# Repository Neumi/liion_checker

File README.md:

# 18650 Battery Checker 
A 18650 Li-Ion battery checker and charger that can be loaded and unloaded by a robotic gripper. Up to 127 devices can be connected on one i2c bus to exchange test results with a master that is connected to a SPS/Arduino/Raspberry Pi.

## Main features:
 - TP4056 charger up to 1A charge current
 - discharging with a programmable constant current sink
 - i2c interconnectivity to other chargers and a master
 - 18650 cells can be placed/removed by a robotic gripper

## Images

### Sorting Machine

### Layout and Board

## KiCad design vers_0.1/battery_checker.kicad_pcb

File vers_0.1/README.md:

# Version 0.1
Basic functionality works. Code is not fully implemented yet.

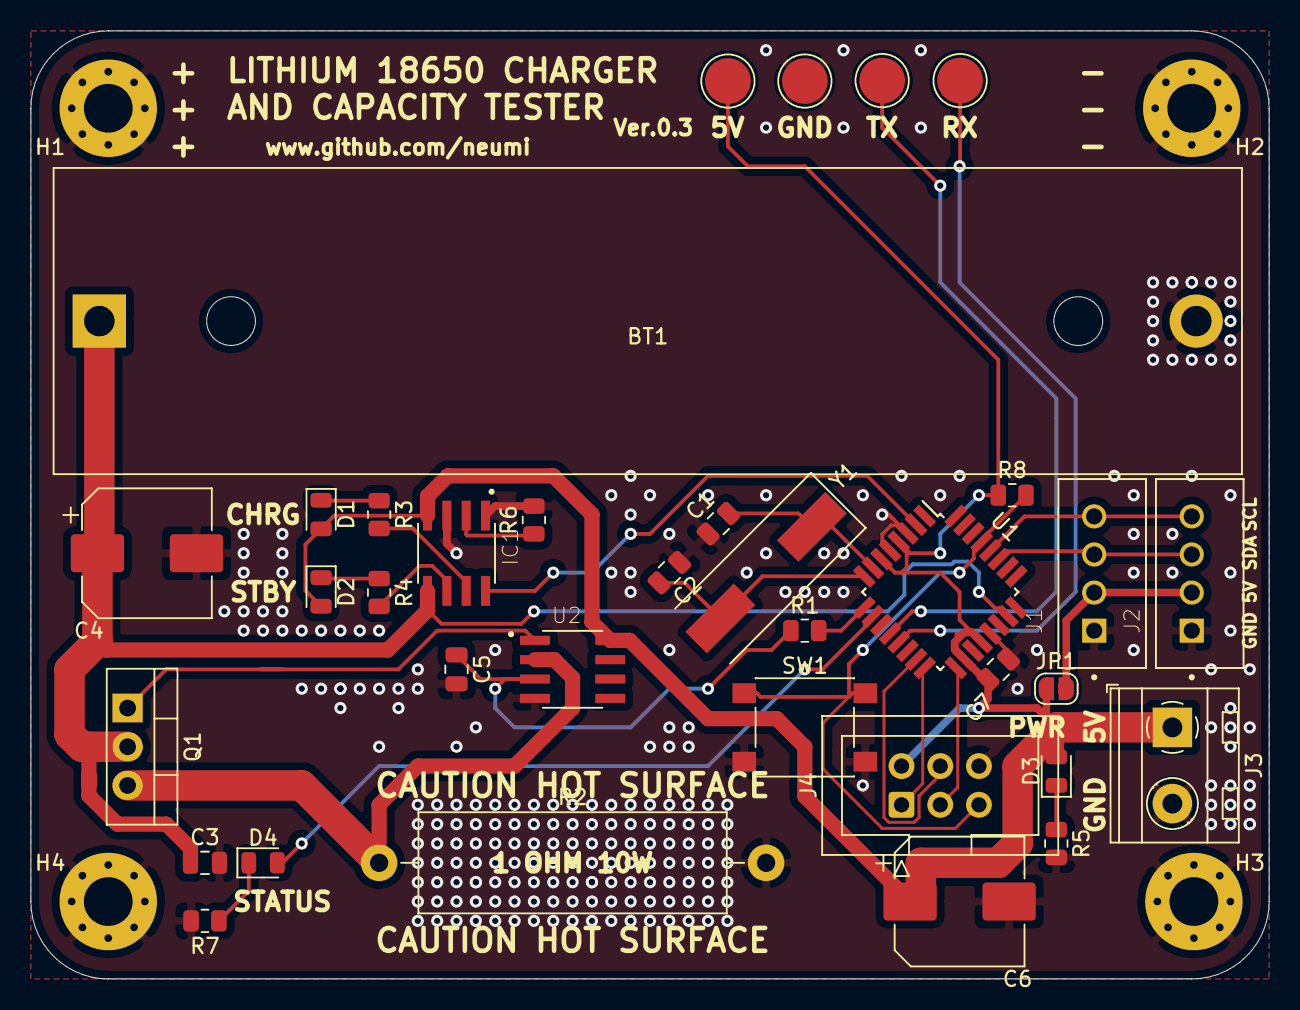
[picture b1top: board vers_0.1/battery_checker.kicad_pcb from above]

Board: 2 copper layers, 81.3 x 62.2 mm, 39 parts (0 on the bottom side), 27 nets.

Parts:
BT1: Battery_Cell; BatteryHolder_MPD_BH-18650-PC2
C1, C2: 22p; C_0805_2012Metric
C3, C5, C7: 100nF; C_0805_2012Metric
C4, C6: 220uF; CP_Elec_8x10
D1: LED_CHRG; LED_0805_2012Metric
D2: LED_STDBY; LED_0805_2012Metric
D3: LED_PWR; LED_0805_2012Metric
D4: LED_STATUS; LED_0805_2012Metric
H1, H2, H3, H4: MountingHole_Pad; MountingHole_3.2mm_M3_Pad_Via
IC1: TP4056; SOIC127P599X175-8N
J1, J2: B4B-XH-A(LF)(SN); JST_B4B-XH-A(LF)(SN)
J3: Conn_01x02_Male; TerminalBlock_MetzConnect_Type094_RT03502HBLU_1x02_P5.00mm_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
J4: AVR-ISP-6; IDC-Header_2x03_P2.54mm_Vertical
JP1: SolderJumper_2_Open; SolderJumper-2_P1.3mm_Open_RoundedPad1.0x1.5mm
Q1: IRLZ44N; TO-220-3_Vertical
R1: 1M; R_0805_2012Metric
R2: 1R5W; R_Axial_Power_L20.0mm_W6.4mm_P25.40mm
R3, R4, R5, R7: 330; R_0805_2012Metric
R6: 1.5k; R_0805_2012Metric
R8: 10k; R_0805_2012Metric
SW1: reset; SW_Push_1P1T_NO_6x6mm_H9.5mm
TP1: 5V; TestPoint_Pad_D3.0mm
TP2: GND; TestPoint_Pad_D3.0mm
TP3: RX; TestPoint_Pad_D3.0mm
TP4: TX; TestPoint_Pad_D3.0mm
U1: ATmega328-AU; TQFP-32_7x7mm_P0.8mm
U2: LM358M_NOPB; SOIC127P599X175-8N
Y1: Crystal; Crystal_SMD_HC49-SD

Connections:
+5V: C6.1, C7.1, D1.2, D2.2, D3.2, IC1.4, J3.1, J4.2, JP1.1, R8.1, TP1.1, U1.4, U1.6, U1.18, U1.20, U2.8
CHRG_enable: IC1.8, U1.2
GND: BT1.2, C1.1, C2.1, C3.2, C4.2, C5.2, C6.2, C7.2, H1.1, H2.1, H3.1, H4.1, IC1.1, IC1.3, J1.1, J2.1, J3.2, J4.6, R2.2, R5.2, R6.2, R7.2, SW1.2, TP2.1, U1.3, U1.5, U1.21, U2.4
LED_STATUS: D4.2, U1.10
MISO: J4.1, U1.16
MOSI: J4.4, U1.15
unnamed: C1.2, U1.7, Y1.1
unnamed: C2.2, U1.8, Y1.2
unnamed: C5.1, R1.1, U2.3
unnamed: D1.1, R3.1
unnamed: D2.1, R4.1
unnamed: D3.1, R5.1
unnamed: D4.1, R7.1
unnamed: IC1.2, R6.1
unnamed: IC1.6, R4.2
unnamed: IC1.7, R3.2
unnamed: J1.2, J2.2, JP1.2
unnamed: Q1.1, U2.1
unnamed: Q1.3, R2.1, U2.2
PWM: R1.2, U1.9
RST: J4.5, R8.2, SW1.1, U1.29
RX: TP3.1, U1.13
SCK: J4.3, U1.17
SCL: J1.4, J2.4, U1.28
SDA: J1.3, J2.3, U1.27
TX: TP4.1, U1.12
v_sens: BT1.1, C3.1, C4.1, IC1.5, Q1.2, U1.23

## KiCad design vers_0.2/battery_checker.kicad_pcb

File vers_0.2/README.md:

# Version 0.2
Version 0.2 is a four battery approach with only one microcontroller that manages charging/discharging/measurements for all four cells at once.

Board needs layout. Schematic is done.

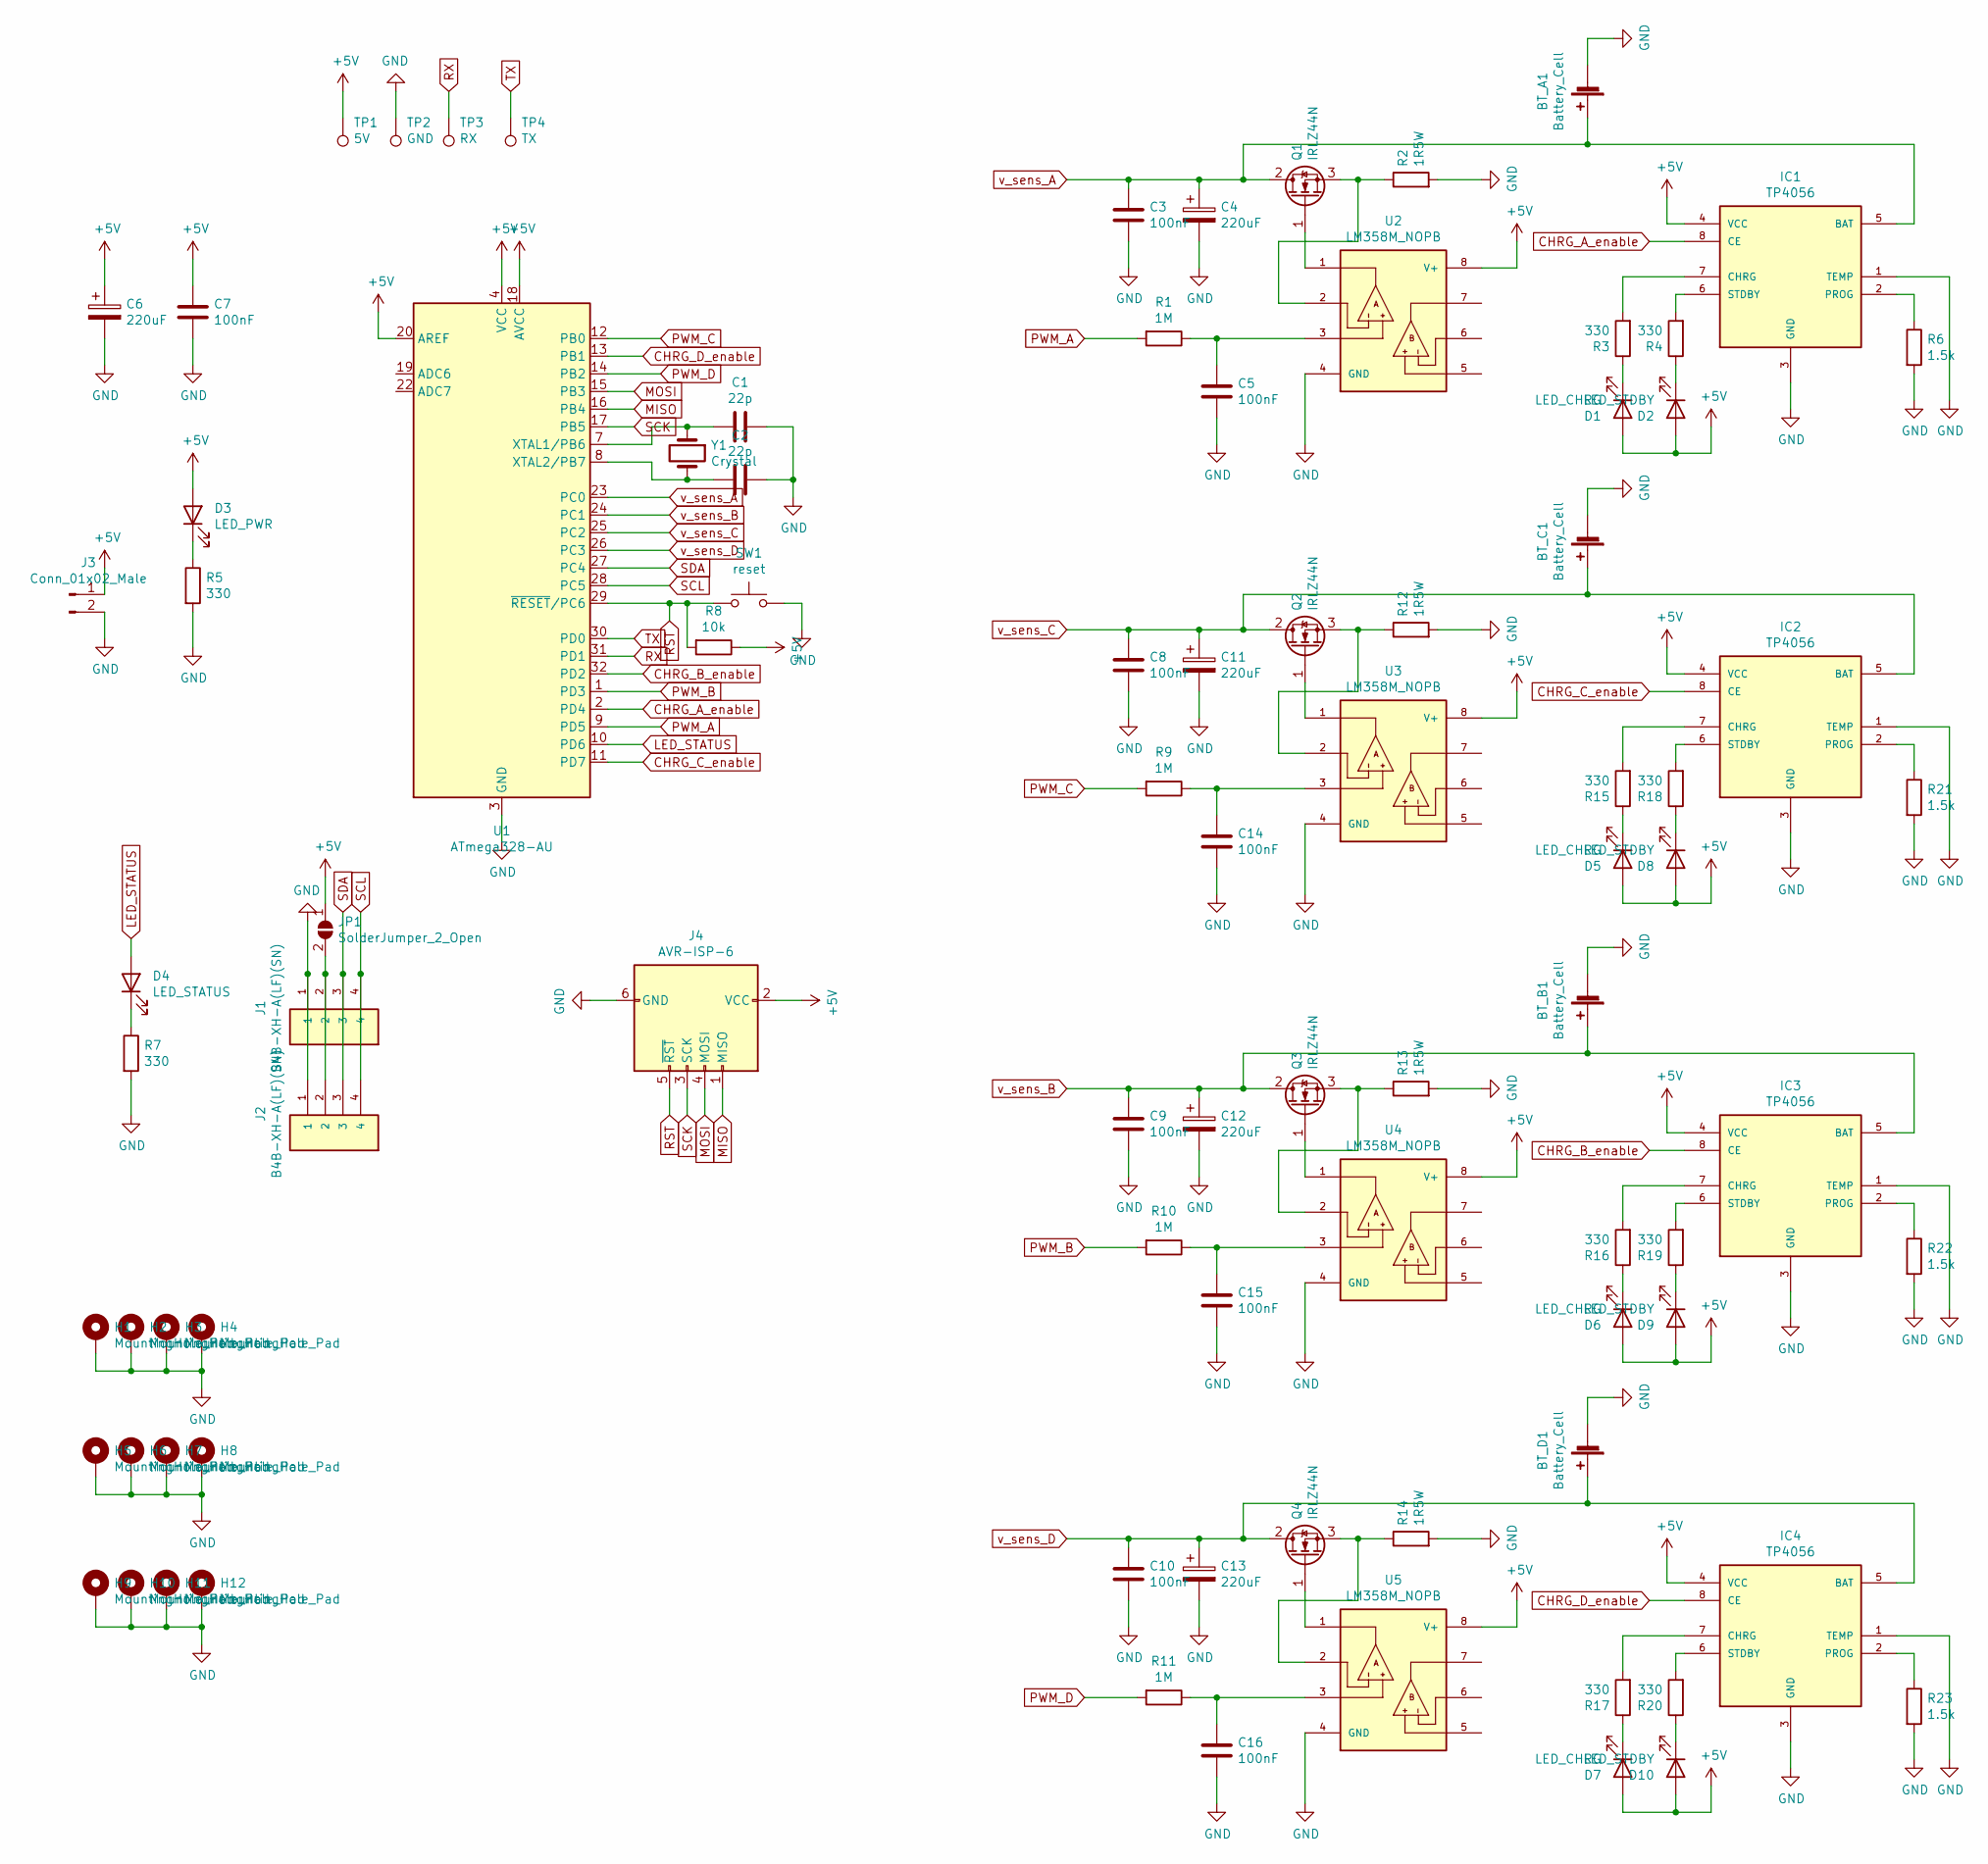
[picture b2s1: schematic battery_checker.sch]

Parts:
BT_A1: Battery_Cell; BatteryHolder_MPD_BH-18650-PC2
BT_B1: Battery_Cell; BatteryHolder_MPD_BH-18650-PC2
BT_C1: Battery_Cell; BatteryHolder_MPD_BH-18650-PC2
BT_D1: Battery_Cell; BatteryHolder_MPD_BH-18650-PC2
C1, C2: 22p; C_0805_2012Metric
C3, C5, C7, C8, C9, C10, C14, C15, C16: 100nF; C_0805_2012Metric
C4, C6, C11, C12, C13: 220uF; CP_Elec_8x10
D1, D5, D6, D7: LED_CHRG; LED_0805_2012Metric
D2, D8, D9, D10: LED_STDBY; LED_0805_2012Metric
D3: LED_PWR; LED_0805_2012Metric
D4: LED_STATUS; LED_0805_2012Metric
H1, H2, H3, H4, H5, H6, H7, H8, H9, H10, H11, H12: MountingHole_Pad; MountingHole_3.2mm_M3_Pad_Via
IC1, IC2, IC3, IC4: TP4056; SOIC127P599X175-8N
J1, J2: B4B-XH-A(LF)(SN); JST_B4B-XH-A(LF)(SN); PARTREV NA
J3: Conn_01x02_Male; TerminalBlock_MetzConnect_Type094_RT03502HBLU_1x02_P5.00mm_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
J4: AVR-ISP-6; IDC-Header_2x03_P2.54mm_Vertical
JP1: SolderJumper_2_Open; SolderJumper-2_P1.3mm_Open_RoundedPad1.0x1.5mm
Q1, Q2, Q3, Q4: IRLZ44N; TO-220-3_Vertical
R1, R9, R10, R11: 1M; R_0805_2012Metric
R2, R12, R13, R14: 1R5W; R_Axial_Power_L20.0mm_W6.4mm_P25.40mm
R3, R4, R5, R7, R15, R16, R17, R18, R19, R20: 330; R_0805_2012Metric
R6, R21, R22, R23: 1.5k; R_0805_2012Metric
R8: 10k; R_0805_2012Metric
SW1: reset; SW_Push_1P1T_NO_6x6mm_H9.5mm
TP1: 5V; TestPoint_Pad_D3.0mm
TP2: GND; TestPoint_Pad_D3.0mm
TP3: RX; TestPoint_Pad_D3.0mm
TP4: TX; TestPoint_Pad_D3.0mm
U1: ATmega328-AU; TQFP-32_7x7mm_P0.8mm
U2, U3, U4, U5: LM358M_NOPB; SOIC127P599X175-8N
Y1: Crystal; Crystal_SMD_HC49-SD

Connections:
+5V: C6.1, C7.1, D1.2 (A), D2.2 (A), D3.2 (A), D5.2 (A), D6.2 (A), D7.2 (A), D8.2 (A), D9.2 (A), D10.2 (A), IC1.4 (VCC), IC2.4 (VCC), IC3.4 (VCC), IC4.4 (VCC), J3.1, J4.2 (VCC), JP1.1 (A), R8.1, TP1.1, U1.4 (VCC), U1.6 (VCC), U1.18 (AVCC), U1.20 (AREF), U2.8 (V+), U3.8 (V+), U4.8 (V+), U5.8 (V+)
CHRG_A_enable: IC1.8 (CE), U1.2 (PD4)
CHRG_B_enable: IC3.8 (CE), U1.32 (PD2)
CHRG_C_enable: IC2.8 (CE), U1.11 (PD7)
CHRG_D_enable: IC4.8 (CE), U1.13 (PB1)
GND: BT_A1.2 (-), BT_B1.2 (-), BT_C1.2 (-), BT_D1.2 (-), C1.1, C2.1, C3.2, C4.2, C5.2, C6.2, C7.2, C8.2, C9.2, C10.2, C11.2, C12.2, C13.2, C14.2, C15.2, C16.2, H1.1, H2.1, H3.1, H4.1, H5.1, H6.1, H7.1, H8.1, H9.1, H10.1, H11.1, H12.1, IC1.1 (TEMP), IC1.3 (GND), IC2.1 (TEMP), IC2.3 (GND), IC3.1 (TEMP), IC3.3 (GND), IC4.1 (TEMP), IC4.3 (GND), J1.1, J2.1, J3.2, J4.6 (GND), R2.2, R5.2, R6.2, R7.2, R12.2, R13.2, R14.2, R21.2, R22.2, R23.2, SW1.2, TP2.1, U1.3 (GND), U1.5 (GND), U1.21 (GND), U2.4 (GND), U3.4 (GND), U4.4 (GND), U5.4 (GND)
LED_STATUS: D4.2 (A), U1.10 (PD6)
MISO: J4.1 (MISO), U1.16 (PB4)
MOSI: J4.4 (MOSI), U1.15 (PB3)
unnamed: C1.2, U1.7 (XTAL1/PB6), Y1.1
unnamed: C2.2, U1.8 (XTAL2/PB7), Y1.2
unnamed: C5.1, R1.1, U2.3
unnamed: C14.1, R9.1, U3.3
unnamed: C15.1, R10.1, U4.3
unnamed: C16.1, R11.1, U5.3
unnamed: D1.1 (K), R3.1
unnamed: D2.1 (K), R4.1
unnamed: D3.1 (K), R5.1
unnamed: D4.1 (K), R7.1
unnamed: D5.1 (K), R15.1
unnamed: D6.1 (K), R16.1
unnamed: D7.1 (K), R17.1
unnamed: D8.1 (K), R18.1
unnamed: D9.1 (K), R19.1
unnamed: D10.1 (K), R20.1
unnamed: IC1.2 (PROG), R6.1
unnamed: IC1.6 (STDBY), R4.2
unnamed: IC1.7 (CHRG), R3.2
unnamed: IC2.2 (PROG), R21.1
unnamed: IC2.6 (STDBY), R18.2
unnamed: IC2.7 (CHRG), R15.2
unnamed: IC3.2 (PROG), R22.1
unnamed: IC3.6 (STDBY), R19.2
unnamed: IC3.7 (CHRG), R16.2
unnamed: IC4.2 (PROG), R23.1
unnamed: IC4.6 (STDBY), R20.2
unnamed: IC4.7 (CHRG), R17.2
unnamed: J1.2, J2.2, JP1.2 (B)
unnamed: Q1.1 (G), U2.1
unnamed: Q1.3 (S), R2.1, U2.2
unnamed: Q2.1 (G), U3.1
unnamed: Q2.3 (S), R12.1, U3.2
unnamed: Q3.1 (G), U4.1
unnamed: Q3.3 (S), R13.1, U4.2
unnamed: Q4.1 (G), U5.1
unnamed: Q4.3 (S), R14.1, U5.2
PWM_A: R1.2, U1.9 (PD5)
PWM_B: R10.2, U1.1 (PD3)
PWM_C: R9.2, U1.12 (PB0)
PWM_D: R11.2, U1.14 (PB2)
RST: J4.5 (~RST), R8.2, SW1.1, U1.29 (~RESET~/PC6)
RX: TP3.1, U1.31 (PD1)
SCK: J4.3 (SCK), U1.17 (PB5)
SCL: J1.4, J2.4, U1.28 (PC5)
SDA: J1.3, J2.3, U1.27 (PC4)
TX: TP4.1, U1.30 (PD0)
v_sens_A: BT_A1.1 (+), C3.1, C4.1, IC1.5 (BAT), Q1.2 (D), U1.23 (PC0)
v_sens_B: BT_B1.1 (+), C9.1, C12.1, IC3.5 (BAT), Q3.2 (D), U1.24 (PC1)
v_sens_C: BT_C1.1 (+), C8.1, C11.1, IC2.5 (BAT), Q2.2 (D), U1.25 (PC2)
v_sens_D: BT_D1.1 (+), C10.1, C13.1, IC4.5 (BAT), Q4.2 (D), U1.26 (PC3)

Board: 2 copper layers, 89 parts (0 on the bottom side), 60 nets, no tracks yet.

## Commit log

2021-02-04 initial commit for v1 and v2
2021-02-04 added images
2021-02-04 added readme for versions
2021-02-08 added imgs
2021-02-09 images changed
2021-02-12 added code
2021-02-15 added capcity checker arduino code
2023-01-13 added gripper STL files
2023-01-13 added image of gripper assebly
